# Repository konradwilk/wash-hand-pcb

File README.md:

# License

The project is under Attribution-ShareAlike 4.0 International (CC BY-SA 4.0).

# Libraries used for this project

 - adafruit
 - darnok\_common (https://github.com/konradwilk/eagle-libraries.git)
 - darnok\_led (https://github.com/konradwilk/eagle-libraries.git)
 - darnok\_usb (https://github.com/konradwilk/eagle-libraries.git)
 - darnok\_sensors (https://github.com/konradwilk/eagle-libraries.git)
 - darnok\_microsd (https://github.com/konradwilk/eagle-libraries.git)
 - darnok\_4050 (https://github.com/konradwilk/eagle-libraries.git)
 - SparkFun-Aesthetics
 - SparkFun-Capacitors
 - SparkFun-Connectors
 - SparkFun-Hardware
 - SparkFun-IC-Microcontroller
 - SparkFun-IC-Power
 - SparkFun-Jumpers
 - Serial-Basic (https://github.com/sparkfun/Serial_Basic_Breakout-CH340G.git)

# Purpose

Quite simply it is to have a count-down timer for 20 seconds for washing hands.
It is activated by a line sensor (which has infrared light) that plugs in the board.

</img>

Video (speed up) of text printed.

# PCB

The _main_ branch is for development and changes often.
The <a href="Wash_Hand.pdf">Wash Hand</a> Board and Schematic are available.

## Prior versions

There are various branches, see:

 - <a href="https://github.com/konradwilk/wash-hand-pcb/tree/stable-1.3-tqfp">stable-1.3-tqfp</a>
 - <a href="https://github.com/konradwilk/wash-hand-pcb/tree/stable-1.3-dip28">stable-1.3-dip28</a>
 - <a href="https://github.com/konradwilk/wash-hand-pcb/tree/stable-1.2-dip28">stable-1.2-dip28</a>

# Future plans for software

In particular order:

 - Fetch data from a SD-card (if attached), otherwise read from EEPROM (1K).
 - Format-type of the data type for above mechanism.
 - Utilize sleep operations to keep the CPU most of the time asleep.
 - Utilize modulo for the numbers.

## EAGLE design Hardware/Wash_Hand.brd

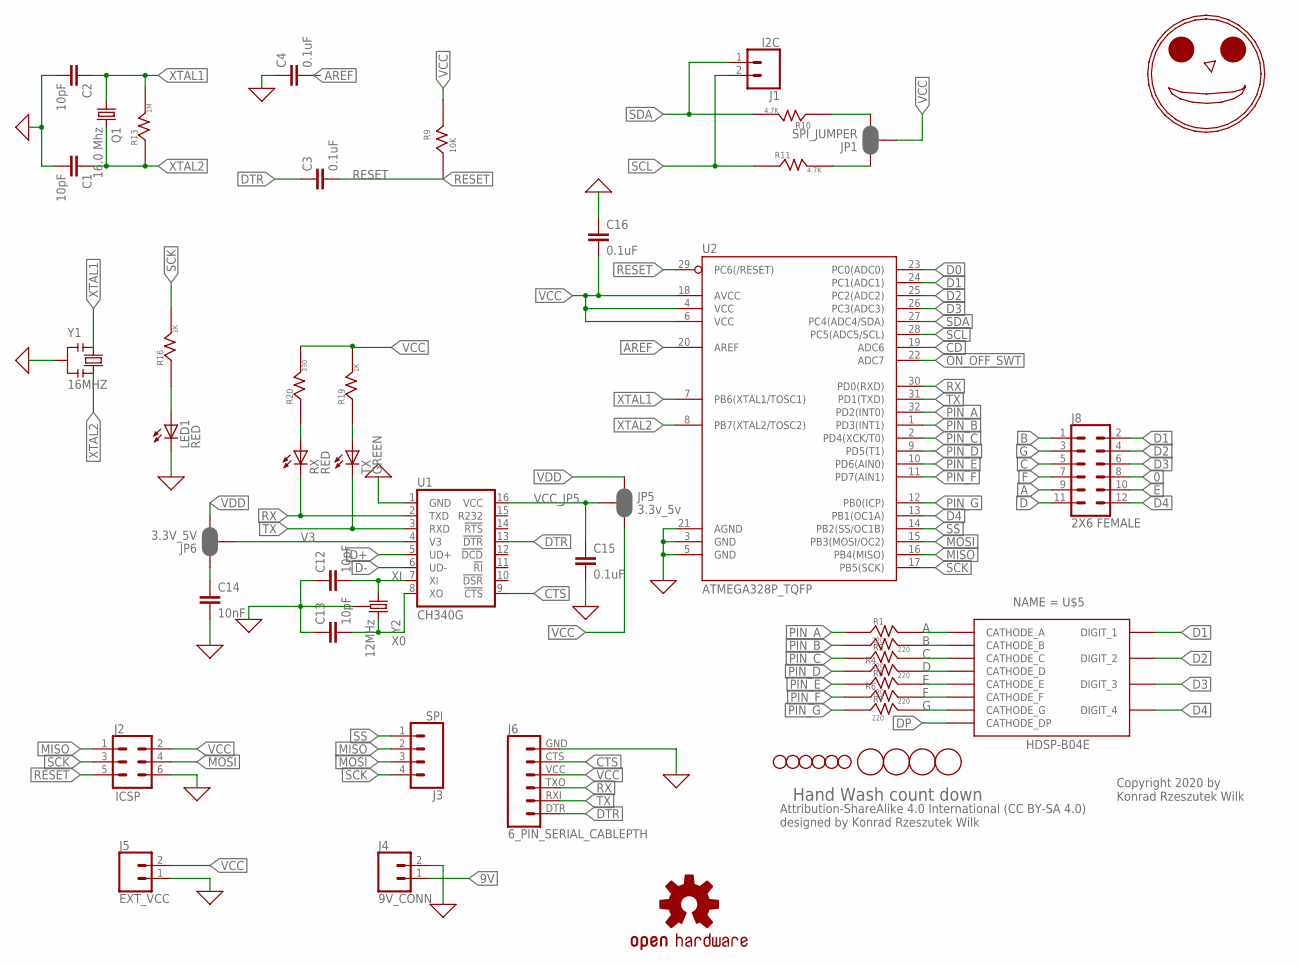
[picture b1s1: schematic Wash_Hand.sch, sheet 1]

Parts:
C1, C2, C12, C13: 10pF; 1206
C3, C4, C15, C16: 0.1uF; 1206
C14: 10nF; 1206
H1, H2, H3, H4, H5, H6: STAND-OFF
J1: I2C; 1X02
J2: ICSP; 2X3
J3: SPI; 1X04
J4: 9V_CONN; 1X02
J5: EXT_VCC; 1X02
J6: 6_PIN_SERIAL_CABLEPTH; FTDI_BASIC
J8: 2X6 FEMALE; 2X6
JP1: SPI_JUMPER; SMT-JUMPER_3_2-NC_PASTE_SILK
JP5: 3.3v_5v; SMT-JUMPER_3_2-NC_PASTE_SILK
JP6: 3.3V_5V; SMT-JUMPER_3_2-NC_PASTE_SILK
LED1: RED; 1206
LOGO1: OSHW-LOGOM; OSHW-LOGO-M
LOGO2: HAPPY_FACE_LOGO
Q1: 16.0 Mhz; HC49/S
R1, R2, R3, R4, R5, R6, R7: 220; 1206
R9: 10K; 1206
R10, R11: 4.7K; 1206
R13: 1M; 1206
R16, R19: 1K; 1206
R20: 330; 1206
RX: RED; 1206
TX: GREEN; 1206
U1: CH340G; SO016
U2: ATMEGA328P_TQFP; TQFP32-08
U$5: HDSP-B04E; HDSP-B0XE
U$7, U$8, U$9, U$10: FIDUCIAL; FIDUCIAL_1MM
Y1: 16MHZ; RESONATOR
Y2: 12MHz; CRYSTAL-SMD-3.2X2.5

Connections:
0: C1.2, C2.2, C4.1, C12.1, C13.1, C14.2, C15.2, C16.1, J2.6, J4.2, J5.1, J6.GND (6), J8.8, LED1.C, U1.1 (GND), U2.3 (GND), U2.5 (GND), U2.21 (AGND), Y1.2, Y2.2 (GND), Y2.4 (GND); also elsewhere on the board
9V: J4.1; also elsewhere on the board
A: J8.9, R1.2 (R_2), U$5.PIN$11 (CATHODE_A)
AREF: C4.2, U2.20 (AREF)
B: J8.1, R2.2 (R_2), U$5.PIN$7 (CATHODE_B)
C: J8.5, R3.2 (R_2), U$5.PIN$4 (CATHODE_C)
CD: U2.19 (ADC6); also elsewhere on the board
CTS: J6.CTS (5), U1.9 (!CTS)
D: J8.11, R4.2 (R_2), U$5.PIN$2 (CATHODE_D)
D0: U2.23 (PC0(ADC0)); also elsewhere on the board
D1: J8.2, U2.24 (PC1(ADC1)), U$5.PIN12 (DIGIT_1)
D2: J8.4, U2.25 (PC2(ADC2)), U$5.PIN$9 (DIGIT_2)
D3: J8.6, U2.26 (PC3(ADC3)), U$5.PIN$8 (DIGIT_3)
D4: J8.12, U2.13 (PB1(OC1A)), U$5.PIN$6 (DIGIT_4)
D+: U1.5 (UD+); also elsewhere on the board
D-: U1.6 (UD-); also elsewhere on the board
DP: U$5.PIN$3 (CATHODE_DP)
DTR: C3.1, J6.DTR (1), U1.13 (!DTR)
E: J8.10, R5.2 (R_2), U$5.PIN$1 (CATHODE_E)
F: J8.7, R6.2 (R_2), U$5.PIN$10 (CATHODE_F)
G: J8.3, R7.2 (R_2), U$5.PIN$5 (CATHODE_G)
MISO: J2.1, J3.2, U2.16 (PB4(MISO)); also elsewhere on the board
MOSI: J2.4, J3.3, U2.15 (PB3(MOSI/OC2)); also elsewhere on the board
unnamed: JP1.3, R10.1 (R_1)
unnamed: JP1.1, R11.2 (R_2)
unnamed: LED1.A, R16.1 (R_1)
unnamed: R19.1 (R_1), TX.A
unnamed: R20.1 (R_1), RX.A
unnamed: C14.1, JP6.1
ON_OFF_SWT: U2.22 (ADC7); also elsewhere on the board
PIN_A: R1.1 (R_1), U2.32 (PD2(INT0))
PIN_B: R2.1 (R_1), U2.1 (PD3(INT1))
PIN_C: R3.1 (R_1), U2.2 (PD4(XCK/T0))
PIN_D: R4.1 (R_1), U2.9 (PD5(T1))
PIN_E: R5.1 (R_1), U2.10 (PD6(AIN0))
PIN_F: R6.1 (R_1), U2.11 (PD7(AIN1))
PIN_G: R7.1 (R_1), U2.12 (PB0(ICP))
RESET: C3.2, J2.5, R9.1 (R_1), U2.29 (PC6(/RESET))
RX: J6.TXO (3), RX.C, U1.2 (TXD), U2.30 (PD0(RXD))
SCK: J2.3, J3.4, R16.2 (R_2), U2.17 (PB5(SCK)); also elsewhere on the board
SCL: J1.2, R11.1 (R_1), U2.28 (PC5(ADC5/SCL))
SDA: J1.1, R10.2 (R_2), U2.27 (PC4(ADC4/SDA))
SS: J3.1, U2.14 (PB2(SS/OC1B)); also elsewhere on the board
TX: J6.RXI (2), TX.C, U1.3 (RXD), U2.31 (PD1(TXD))
V3: JP6.2, U1.4 (V3)
VCC: C16.2, J2.2, J5.2, J6.VCC (4), JP1.2, JP5.3, R9.2 (R_2), R19.2 (R_2), R20.2 (R_2), U2.4 (VCC), U2.6 (VCC), U2.18 (AVCC); also elsewhere on the board
VCC_JP5: C15.1, JP5.2, U1.16 (VCC)
VDD: JP5.1, JP6.3; also elsewhere on the board
X0: C13.2, U1.8 (XO), Y2.3 (2)
XI: C12.2, U1.7 (XI), Y2.1
XTAL1: C2.1, Q1.1, R13.2 (R_2), U2.7 (PB6(XTAL1/TOSC1)), Y1.1
XTAL2: C1.1, Q1.2, R13.1 (R_1), U2.8 (PB7(XTAL2/TOSC2)), Y1.3

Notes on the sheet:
Hand Wash count down
Copyright 2020 by Konrad Rzeszutek Wilk
Attribution-ShareAlike 4.0 International (CC BY-SA 4.0) designed by Konrad Rzeszutek Wilk

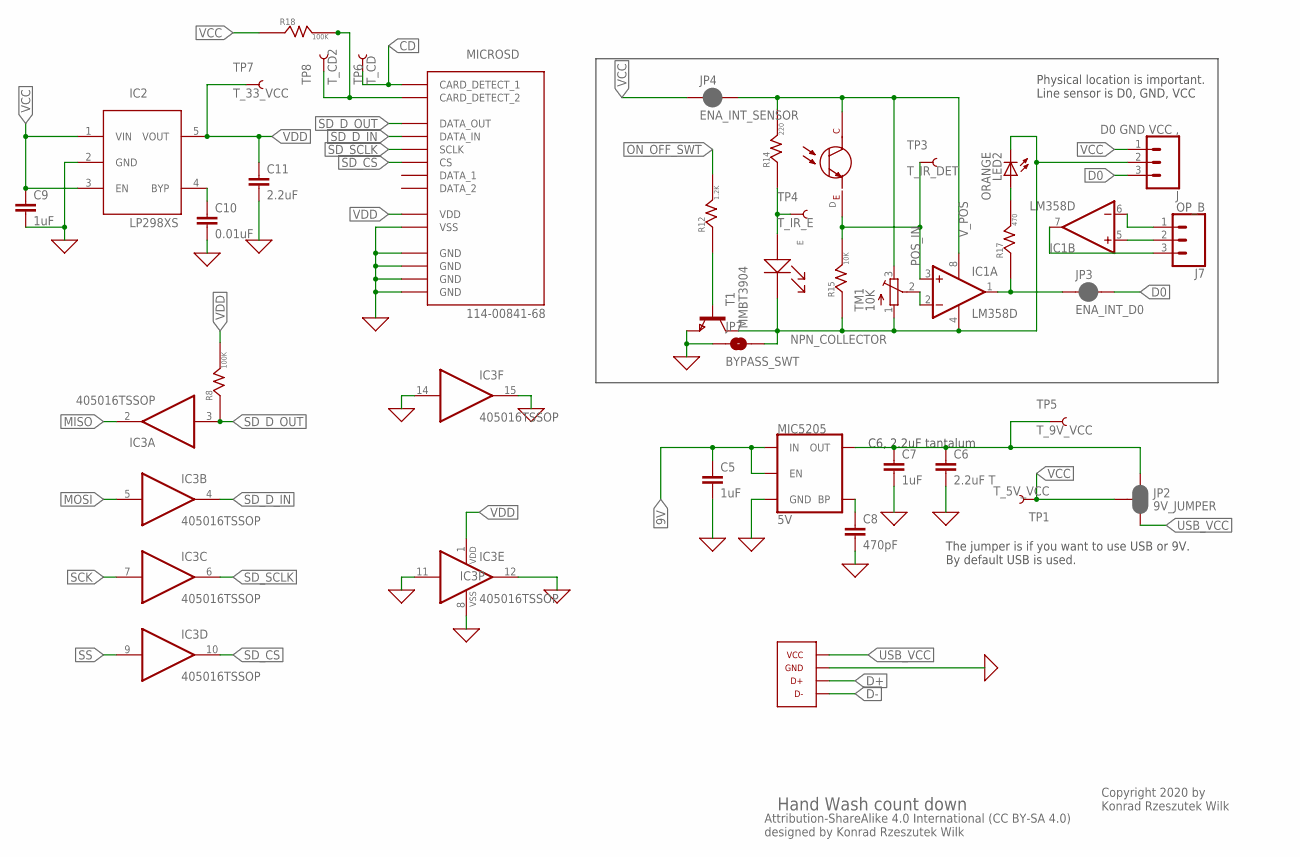
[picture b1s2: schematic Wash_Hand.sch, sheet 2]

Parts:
C5, C7, C9: 1uF; 1206
C6: 2.2uF T; 1206
C8: 470pF; 1206
C10: 0.01uF; 1206
C11: 2.2uF; 1206
D: LTR-301
E: LTE-302
IC1: LM358D; SO08
IC2: LP298XS; SOT23-5L
IC3: 405016TSSOP; TSSOP16
J: D0 GND VCC ,; 1X03
J7: OP_B; 1X03
JP2: 9V_JUMPER; SMT-JUMPER_3_2-NC_PASTE_SILK
JP3: ENA_INT_D0; SMT-JUMPER_2_NC_PASTE_SILK
JP4: ENA_INT_SENSOR; SMT-JUMPER_2_NC_PASTE_SILK
JP7: BYPASS_SWT; SMT-JUMPER_2_NO_SILK
LED2: ORANGE; 1206
MIC5205: 5V; SOT23-5
MICROSD: 114-00841-68
R8, R18: 100K; 1206
R12: 1.2K; 1206
R14: 220; 1206
R15: 10K; 1206
R17: 470; 1206
T1: MMBT3904; SOT-23
TM1: 10K; TC33X
TP1: T_5V_VCC; PAD.03X.04
TP3: T_IR_DET; PAD.03X.04
TP4: T_IR_E; PAD.03X.04
TP5: T_9V_VCC; PAD.03X.04
TP6: T_CD; PAD.03X.04
TP7: T_33_VCC; PAD.03X.04
TP8: T_CD2; PAD.03X.04
U$4: USB_MICROB_10118194_AMPHENOL

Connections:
0: C5.2, C6.2, C7.2, C8.2, C9.2, C10.2, C11.2, IC2.2 (GND), IC3.8 (VSS), IC3.11 (I), IC3.12 (O), IC3.14 (I), IC3.15 (O), JP7.1, MIC5205.2 (GND), MICROSD.GND$1 (GND), MICROSD.GND$2 (GND), MICROSD.GND$3 (GND), MICROSD.GND$4 (GND), MICROSD.VSS, T1.2 (E), U$4.5 (GND); also elsewhere on the board
9V: C5.1, MIC5205.1 (IN), MIC5205.3 (EN); also elsewhere on the board
CD: MICROSD.CD_SW_1 (CARD_DETECT_1), TP6.P$1; also elsewhere on the board
D0: IC1.1 (OUT), J.3, JP3.1, JP3.2, R17.1 (R_1); also elsewhere on the board
D+: U$4.3 (D+); also elsewhere on the board
D-: U$4.2 (D-); also elsewhere on the board
MISO: IC3.2 (O); also elsewhere on the board
MOSI: IC3.5 (I); also elsewhere on the board
unnamed: IC1.7 (OUT), J7.3
unnamed: MICROSD.CD_SW_2 (CARD_DETECT_2), R18.2 (R_2), TP8.P$1
unnamed: IC1.5 (+IN), J7.2
unnamed: C6.1, C7.1, JP2.1, MIC5205.5 (OUT), TP5.P$1
unnamed: E.A, R14.1 (R_1), TP4.P$1
unnamed: C10.1, IC2.4 (BYP)
unnamed: IC1.6 (-IN), J7.1
unnamed: LED2.A, R17.2 (R_2)
unnamed: R12.1 (R_1), T1.3 (B)
unnamed: C8.1, MIC5205.4 (BP)
NEG_IN: IC1.2 (-IN), TM1.2 (S)
NPN_COLLECTOR: E.C, IC1.4 (V-), J.2, JP7.2, LED2.C, R15.1 (R_1), T1.1 (C), TM1.1 (A)
ON_OFF_SWT: R12.2 (R_2); also elsewhere on the board
POS_IN: D.E, IC1.3 (+IN), R15.2 (R_2), TP3.P$1
SCK: IC3.7 (I); also elsewhere on the board
SD_CS: IC3.10 (O), MICROSD.CS
SD_D_IN: IC3.4 (O), MICROSD.DATA_IN
SD_D_OUT: IC3.3 (I), MICROSD.DATA_OUT, R8.1 (R_1)
SD_SCLK: IC3.6 (O), MICROSD.SCLK
SS: IC3.9 (I); also elsewhere on the board
USB_VCC: JP2.3, U$4.1 (VCC)
VCC: C9.1, IC2.1 (VIN), IC2.3 (EN), J.1, JP2.2, JP4.1, R18.1 (R_1), TP1.P$1; also elsewhere on the board
VDD: C11.1, IC2.5 (VOUT), IC3.1 (VDD), MICROSD.VDD, R8.2 (R_2), TP7.P$1; also elsewhere on the board
V_POS: D.C, IC1.8 (V+), JP4.2, R14.2 (R_2), TM1.3 (E)

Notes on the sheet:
Hand Wash count down
Copyright 2020 by Konrad Rzeszutek Wilk
Attribution-ShareAlike 4.0 International (CC BY-SA 4.0) designed by Konrad Rzeszutek Wilk
Physical location is important. Line sensor is D0, GND, VCC
The jumper is if you want to use USB or 9V. By default USB is used.
C6, 2.2uF tantalum

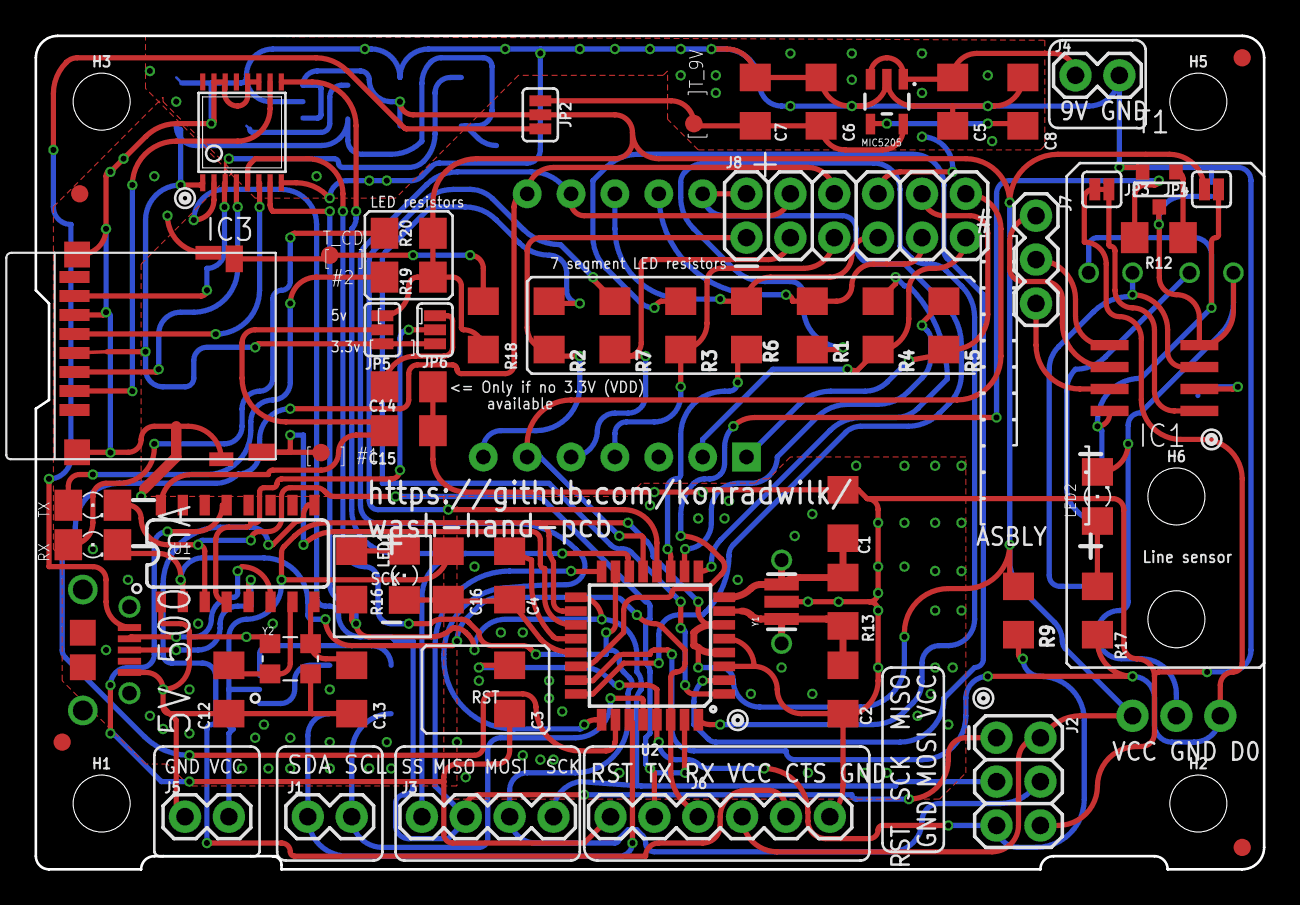
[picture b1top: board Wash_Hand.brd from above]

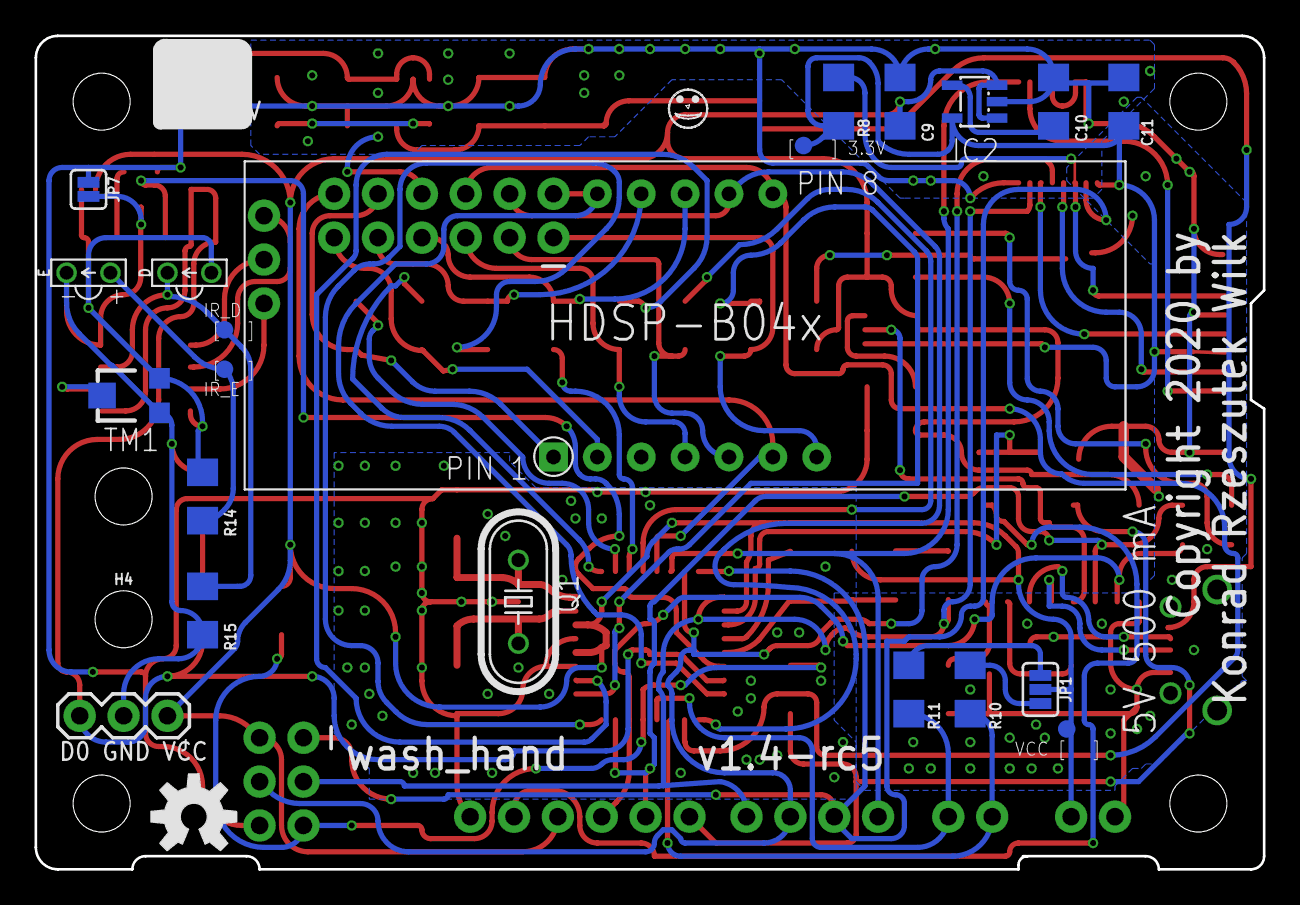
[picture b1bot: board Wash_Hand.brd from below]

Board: 2 copper layers, 71.1 x 48.3 mm, 91 parts (24 on the bottom side), 70 nets.

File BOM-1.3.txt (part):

Partlist exported from /home/konrad/eagle-projects/COVID19-WashHands/Hardware/Wash_Hand_v1.3.sch at 8/14/20 10:20 PM

Qty Value                        Device                        Package                       Parts                           Description                                                                                                                                                                                                                                             HDSP-B04E MF MPN OC_FARNELL OC_NEWARK POPULARITY PROD_ID    VALUE     
1                                CONN_02                       1X02                          J4                              Multi connection point. Often used as Generic Header-pin footprint for 0.1 inch spaced/style header connections                                                                                                                                                                                                               
1   0.01uF                       1.0UF-1206-50V-10%            1206                          C10                             1µF ceramic capacitors                                                                                                                                                                                                                                                                                   CAP-09822  1.0uF     
2   0.1uF                        1.0UF-1206-50V-10%            1206                          C3, C4                          1µF ceramic capacitors                                                                                                                                                                                                                                                                                   CAP-09822  1.0uF     
1   100K                         RESISTORR1206                 1206                          R8                                                                                                                                                                                                                                                                                                                                                            
2   10K                          RESISTORR1206                 1206                          R9, U$1                                                                                                                                                                                                                                                                                                                                                       
1   10K                          TRIMPOTTC33X                  TC33X                         TM1                             SMT trimmer potentiometer part number TC33X                                                                                                                                                                                                                                                                                   
1   114-00841-68                 114-00841-68                  114-00841-68                  MICROSD                         Amphenol MicroSD Push Pull                                                                                                                                                                                                                                                                                                    
1   16.0 Mhz                     CRYSTALHC49S                  HC49/S                        Q1                              CRYSTAL                                                                                                                                                                                                                                                                  1667008    unknown                                   
3   1uF                          1.0UF-1206-50V-10%            1206                          C5, C7, C9                      1µF ceramic capacitors                                                                                                                                                                                                                                                                                   CAP-09822  1.0uF     
2   2.2uF                        1.0UF-1206-50V-10%            1206                          C6, C8                          1µF ceramic capacitors                                                                                                                                                                                                                                                                                   CAP-09822  1.0uF     
8   220                          RESISTORR1206                 1206                          R1, R2, R3, R4, R5, R6, R7, U$2                                                                                                                                                                                                                                                                                                                               
2   22pF                         10UF-1206-6.3V-20%            1206                          C1, C2                          10.0µF ceramic capacitors                                                                                                                                                                                                                                                                                CAP-10057  10uF      
1   328P                         ATMEGA328P_PDIP               DIP28                         U1                              Atmel 328P                                                                                                                                                                                                                                                                                               IC-09136   328P      
2   4.7K                         RESISTORR1206                 1206                          R10, R11                                                                                                                                                                                                                                                                                                                                                      
1   4050D                        4050D                         SO16                          IC3                             Hex non-inverting BUFFER                                                                                                                                                                                                                                                                      6                               
1   470pF                        1.0UF-1206-50V-10%            1206                          C11                             1µF ceramic capacitors                                                                                                                                                                                                                                                                                   CAP-09822  1.0uF     
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
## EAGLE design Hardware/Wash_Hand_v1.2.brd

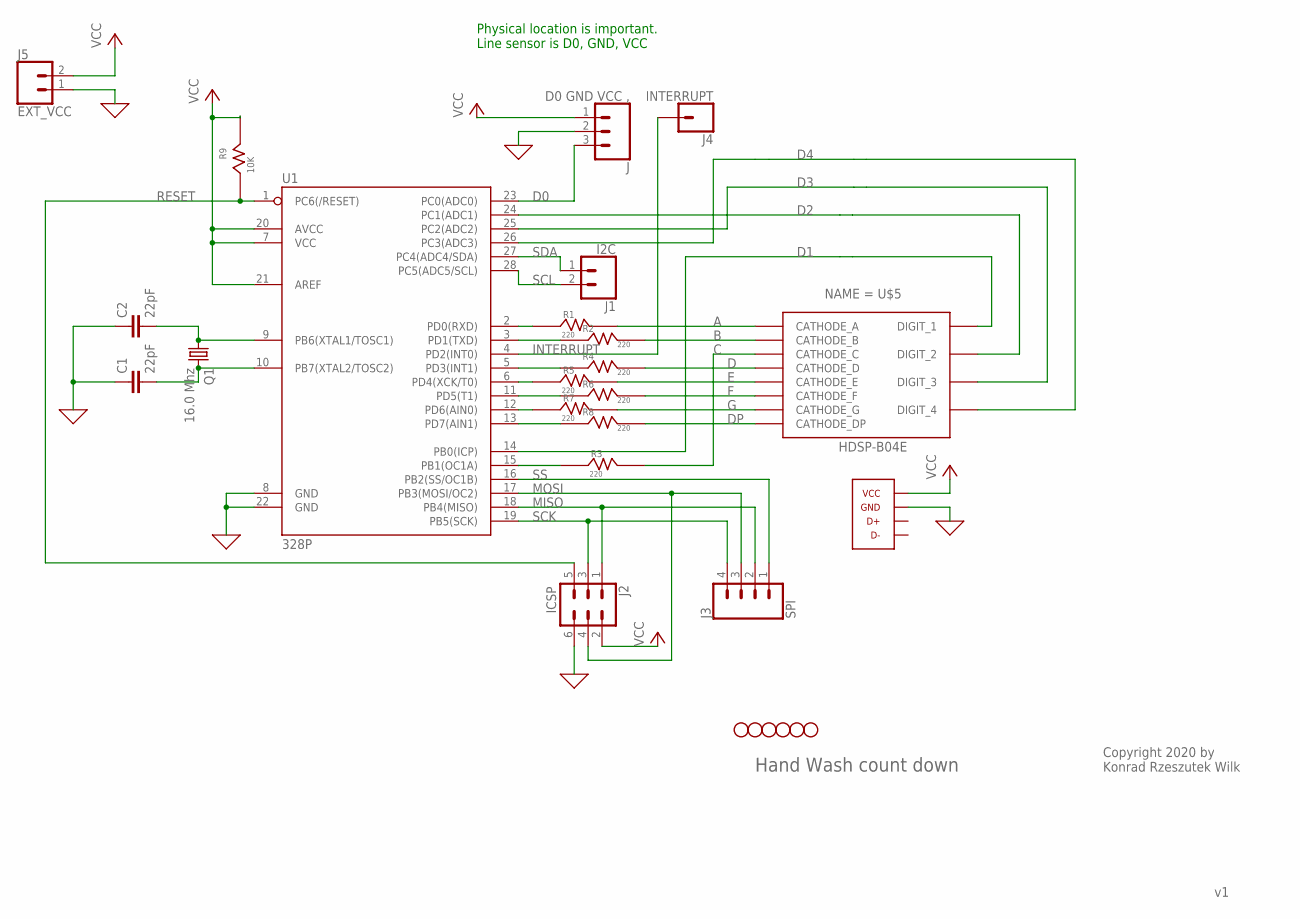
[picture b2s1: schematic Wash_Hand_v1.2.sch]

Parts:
C1, C2: 22pF; CAP-PTH-2.54
H1, H2, H3, H4, H5, H6: STAND-OFF
J: D0 GND VCC ,; 1X03
J1: I2C; 1X02
J2: ICSP; 2X3
J3: SPI; 1X04
J4: INTERRUPT; 1X01
J5: EXT_VCC; 1X02
Q1: 16.0 Mhz; HC49/S
R1, R2, R3, R4, R5, R6, R7, R8: 220; RESISTOR
R9: 10K; RESISTOR
U1: 328P; DIP28
U$4: USB_MICROB_10118194_AMPHENOL
U$5: HDSP-B04E; HDSP-B0XE

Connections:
0: C1.1, C2.1, J.2, J2.6, J5.1, U1.8 (GND), U1.22 (GND), U$4.5 (GND)
A: R1.R_2, U$5.PIN$11 (CATHODE_A)
B: R2.R_2, U$5.PIN$7 (CATHODE_B)
C: R3.R_2, U$5.PIN$4 (CATHODE_C)
D: R4.R_2, U$5.PIN$2 (CATHODE_D)
D0: J.3, U1.23 (PC0(ADC0))
D1: U1.14 (PB0(ICP)), U$5.PIN12 (DIGIT_1)
D2: U1.24 (PC1(ADC1)), U$5.PIN$9 (DIGIT_2)
D3: U1.25 (PC2(ADC2)), U$5.PIN$8 (DIGIT_3)
D4: U1.26 (PC3(ADC3)), U$5.PIN$6 (DIGIT_4)
DP: R8.R_2, U$5.PIN$3 (CATHODE_DP)
E: R5.R_2, U$5.PIN$1 (CATHODE_E)
F: R6.R_2, U$5.PIN$10 (CATHODE_F)
G: R7.R_2, U$5.PIN$5 (CATHODE_G)
INTERRUPT: J4.1, U1.4 (PD2(INT0))
MISO: J2.1, J3.2, U1.18 (PB4(MISO))
MOSI: J2.4, J3.3, U1.17 (PB3(MOSI/OC2))
unnamed: R3.R_1, U1.15 (PB1(OC1A))
unnamed: R1.R_1, U1.2 (PD0(RXD))
unnamed: R5.R_1, U1.6 (PD4(XCK/T0))
unnamed: R7.R_1, U1.12 (PD6(AIN0))
unnamed: C1.2, Q1.2, U1.10 (PB7(XTAL2/TOSC2))
unnamed: C2.2, Q1.1, U1.9 (PB6(XTAL1/TOSC1))
unnamed: R8.R_1, U1.13 (PD7(AIN1))
unnamed: R6.R_1, U1.11 (PD5(T1))
unnamed: R4.R_1, U1.5 (PD3(INT1))
unnamed: R2.R_1, U1.3 (PD1(TXD))
RESET: J2.5, R9.R_1, U1.1 (PC6(/RESET))
SCK: J2.3, J3.4, U1.19 (PB5(SCK))
SCL: J1.2, U1.28 (PC5(ADC5/SCL))
SDA: J1.1, U1.27 (PC4(ADC4/SDA))
SS: J3.1, U1.16 (PB2(SS/OC1B))
VCC: J.1, J2.2, J5.2, R9.R_2, U1.7 (VCC), U1.20 (AVCC), U1.21 (AREF), U$4.1 (VCC)

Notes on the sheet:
Physical location is important. Line sensor is D0, GND, VCC
Hand Wash count down
Copyright 2020 by Konrad Rzeszutek Wilk

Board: 2 copper layers, 27 parts (3 on the bottom side), 33 nets, no tracks yet.

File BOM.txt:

Partlist exported from /home/opc/EAGLE/projects/COVID19-WashHands/Hardware/Wash_Hand_v1.2-routing.sch at 7/14/20 2:54 AM

Qty Value                        Device                       Package                      Parts                          Description                                                                                                      HDSP-B04E MF MPN OC_FARNELL OC_NEWARK PROD_ID    VALUE     
1   10K                          RESISTOR                     RESISTOR                     R9                                                                                                                                                                                                         
1   16.0 Mhz                     CRYSTALHC49S                 HC49/S                       Q1                             CRYSTAL                                                                                                                           1667008    unknown                        
8   220                          RESISTOR                     RESISTOR                     R1, R2, R3, R4, R5, R6, R7, R8                                                                                                                                                                             
2   22pF                         22PF-PTH-2.54MM-200V-5%      CAP-PTH-2.54                 C1, C2                         22pF ceramic capacitors                                                                                                                                CAP-09128  22pF      
1   328P                         ATMEGA328P_PDIP              DIP28                        U1                             Atmel 328P                                                                                                                                             IC-09136   328P      
1   D0    GND  VCC  ,            CONN_03                      1X03                         J                              Multi connection point. Often used as Generic Header-pin footprint for 0.1 inch spaced/style header connections                                                             
1   EXT_VCC                      CONN_02                      1X02                         J5                             Multi connection point. Often used as Generic Header-pin footprint for 0.1 inch spaced/style header connections                                                             
1   HDSP-B04E                    HDSP-B04E                    HDSP-B0XE                    U$5                            7 Segment LED light 0.56"                                                                                                                                                   
1   I2C                          CONN_02                      1X02                         J1                             Multi connection point. Often used as Generic Header-pin footprint for 0.1 inch spaced/style header connections                                                             
1   ICSP                         CONN_03X2FEMALE              2X3                          J2                             Multi connection point. Often used as Generic Header-pin footprint for 0.1 inch spaced/style header connections                                        CONN-11566 FEMALE 2x3
1   INTERRUPT                    CONN_01                      1X01                         J4                             Single connection point. Often used as Generic Header-pin footprint for 0.1 inch spaced/style header connections                                                            
1   SPI                          CONN_04                      1X04                         J3                             Multi connection point. Often used as Generic Header-pin footprint for 0.1 inch spaced/style header connections                                        CONN-09696           
6   STAND-OFF                    STAND-OFF                    STAND-OFF                    H1, H2, H3, H4, H5, H6         Stand Off                                                                                                                                                                   
1   USB_MICROB_10118194_AMPHENOL USB_MICROB_10118194_AMPHENOL USB_MICROB_10118194_AMPHENOL U$4

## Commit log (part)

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2020-07-14 LICENSE: Attribution-ShareAlike 4.0 International (CC BY-SA 4.0).
2020-07-14 Initial schematic and board design.
    v1.1 is bad. I made the auto-routing , added some new items and it has
    now no linking to the schematic. Ignore it.
    v1.2 is the right one.
2020-07-14 Software: Add SPDX
2020-07-14 Initial README file outlaying the ambitions of this project.
2020-07-14 README: Include BOM and URL to line sensor
2020-07-23 Hardware: Split out using darnok_[common,led,usb] instead of the single one.
    As the darnok_misc is going away.
2020-07-23 Hardware: Switch to TQFP32 on ATMEGA328P
2020-07-23 Hardware: Add resistors (4.7K) for the I2C along with a pad.
    The pad is there in case we don't want to use the pull-up
    resistors.
2020-07-23 Hardware: Add OSHW Logo.
2020-07-23 Schematic: Move the information tag to tDoc layer.
2020-07-23 README: Update the list of libraries we use.
2020-07-28 v1.2: Assembly notes.
    Biggest issues:
    - Missing PIN1 label on the ICSP header.
    - The ICSP header should be turned 90
    - Holes for the LED are mighty small
    - No 0.1 uF between pin 7,8 and 20,22
    - Putting in a ATMEGA328P from a Uno works, but programming via SPI no go.
2020-07-29 Makefile: Add makefile using arduino-cli
    Installation:
    https://arduino.github.io/arduino-cli/installation/
2020-07-29 software: Remove the spaces
2020-07-29 Software: Move all the GPIO code in seperate header.
2020-07-30 Software: Add USB only interface
    To easy in debugging.
2020-07-30 Software: s/NOBODY/INIT/
    Better name.
2020-07-30 Software: Add debug_error to signal issues
    We should not hit those code paths - but if we do
    print out the line number.
2020-07-30 Software: Add delay for the second digit (1x, 20)
    Otherwise it would be less brigther than the other one.
2020-07-30 Software: debug: Add __LINE__
    to make it easier to troubleshoot where it is in the code.
2020-07-30 TODO: The code could be improved.
2020-07-30 Notes: For programming with USB we will need RX, TX pins
    But those are used for PINA, and PINB so we will need
    to relocate those two. We don't use DP.
2020-08-01 Schematic: Move the HDSP-B04E to v1.2 location.
    As we also want to re-use the same case for both versions.
2020-08-01 v1.3: Remove INT and DP connection, and attach A, B pins to
2020-08-02 Board/Schematic: Add SCK label and connect to pins
2020-08-03 Board Schematic: Add SS and connect the headers to this label
2020-08-03 Schematic: Move the SPI header to its own location
2020-08-03 Schematic: Add junction on the ground plane.
2020-08-03 Schematic: Move HDSP-B04E and do some cleanups.
2020-08-03 Schematic: Add decoupling capacitor on the VREF.
2020-08-03 Board: Add FTDI basic (6 pin).
    And connect them all.
2020-08-03 Board: Move text around as pin placement will poke through it.
2020-08-04 Board/Schematic: Add line sensor.
    We are using QRE1113GR.
2020-08-07 Board: Change to different line sensor.
    We are going to use discrete parts:
    - LTE-302, LTR-301 (IR emitter and detector).
    - TC33X-2-103E 10K pot
    - LM358DR
    - Bunch of SMD resistors
    This should us give better range.
2020-08-08 Schematic: Add extra sheet.
    We can't just fit any more on just one.
2020-08-08 Board: Adjust the D0_JUMPER,VCC_JUMPER, SPI_JUMPER to the right.
2020-08-09 Board/Schematic: s/VCC/VCC label/
    As that makes it easier to switch in/out componets.
2020-08-10 Board: Move parts around so capacitors are close to LP298 and MIC52055
    Both specs say that capacitors have to be within 0.5 inch.
2020-08-10 Board: All test points have text around them.
2020-08-10 Board: Move Copyright and update date.
2020-08-10 Board/Schematic: Add 470pF bypass to MIC5205
    And also change the Cout to be 2.2uF
2020-08-11 Board: Remove little space for fingers to eject MicroSD card.
2020-08-12 Board/Schematic: Add ATMEGA328P TQFP with goal of replacing DIP28
    .. so that we can swap in and out the DIP28 or TQFP for the prototype
    builds.
2020-08-15 Board: Routing #1
    - We moved a lot of resistors and capacitors around to be
    closer.
    - Realized we can do two "v1.3" - one with a DIP28 and
    one with TQFP. Most of the routes would hopefully lead to the
    right locations.
2020-08-15 Schematic: Fix C5 not being connected (found during routing).
    Somehow the lines did not connect so it just ended up being
    not connected. This fixes it.
2020-08-15 Revert: "Board/Schematic: Add ATMEGA328P TQFP with goal of replacing DIP28"
    .. with the rest of the items to not confuse readers.
2020-08-15 Board: Use the TQFP instead of DIP-28. Change version to have -b postfix.
2020-08-16 Documentation: Update on v1.3a board.
2020-08-26 README: Fix up version number (it is 1.3b)
2020-09-02 Board: Make the SMD register names smaller.
    They are huge.
2020-09-02 Board/Schematic: Update to v1.3b.1
2020-09-02 Board/Schematic: Swap out 4050 to 16TSSOP
    instead of the more bulkier SOP16
2020-09-03 Board: Add + for the tantalum capacitor
2020-09-03 Board: Add PIN1 easy dot for LM358 and ATMEGA328P
2020-09-05 Schematic: PIN1 on LP298 was not hooked to VCC
    .. but it was on the board!
2020-09-05 Schematic: Nothing is connected to ADC6,7 so delete the nets.
2020-09-05 Schematic: Update libraries ...
2020-09-05 Board/Schematic: Update to v1.3b_rc4
2020-09-07 Software: Fix the warnings over __LINE__
2020-09-07 Software: We are using v1.3 ports
2020-09-09 Board/Schematic: Change 22pf to 10pf
    Which makes the crystal work..
2020-09-14 Software: Debug mode - only print 1,2,3,8 once and then
    go in regular mode.
2020-09-15 Board/Schematic: Fix the 16MHz/10pF capacitors.
    The way they are were in the schematic looked right.
    Two capacitors off the crystal. Both capacitors go to
    ground. Except that what Eagle decided it should be was:
    XTAL1 XTAL2
    | |
    +--[CRYSTAL]--+
2020-09-15 Board: Swap C7 with C9.
    The LP298 has C9,C10,C11 but in the board right next to it are:
    _C7_,C10,C11!
    The MIC5205 has C5,C6,C7,C8 but in the board right next to it
    are: C5,C6,_C9_, and C8.
    Lets swap them around to be closer to their own circuits.
2020-09-16 Software: Add USBasp upload
2020-09-16 Release: v1.3a.3
2020-09-16 Board/Schematic: Add resonator (on top of crystal)
    So that we can use either the resonator or
    the crystal+capacitor.
2020-09-22 Board: Add USB ground plane.
    And connect it with the other two.
2020-09-22 Board: Add ground plane for 9V and 3.3V power plants
    They are connected up there..
2020-09-22 Remove the old versions (v1.2, v1.1, and v1).
    If folks want to see them, there will be branches:
    stable-1.2 (DIP28)
    stable-1.3-dip28 (DIP28)
    stable-1.3-tqfp
2020-09-22 Wash_Hand v1.3 -> Wash_Hand
    since we are using Git the release name does not make much sense
    anymore.
2020-09-22 Board: Flip 7Segment resistors
    .. and also some DRC errors.
2020-09-22 Board: Fixup the registers name and values.
    Align the names and values to be next to each other.
2020-09-22 Board/Schematic: Major rework:
    - Move the TQFP so that we can have the crystal right next to it.
    - Move most of the data lines to one side of the board.
    - Move resistors / capacitors around around the components
    - Make the wires 0.012 instead of 0.006 (or 0.008).
    - Also while we are it, make the turns more curved.
    Next:
2020-09-22 Board/Schematic: Update RELEASE to be main
    As that is the current release train.
2020-09-22 Release: By default assume Hardware/Wash_Hand.sch
    in case that is not provided.
2020-09-22 Release: Remove the print option
    And instead run the print.scr
2020-09-22 Software: Add printk(..)
    to make it easier to write strings.
2020-09-22 USBAsp: Corruptions on verify
    .. are sometimes seen. Doing a full erase flash fixes
    the issue.
2020-09-24 Software: DEBUG - make printing faster..
    to easy debugging.
2020-09-25 Board/Schematic: Add a LED on the line-sensor
    ..when we have detected a change.
2020-09-25 RELEASE-1.4-rc0
2020-10-16 Schematic/Board: Move the CH340 to right and use smaller 12Mhz SMD clock
2020-10-17 Board/Hardware: Add 5V support for CH340
    ..which requires adding jumpers and a capacitor (0.01uF).
    While at it, add the power decoupling one for VCC.
2020-10-17 Schematic/Board: Add 100nF decoupling capacitor to AVCC
2020-10-17 RELEASE-1.4-rc1
2020-10-31 Software: Build always with DEBUG, NOSD, and Watchdog.
2020-10-31 Makefile: Roll up the various defines and define variables
2020-11-04 Makefile: Target for ATMEGA8 as well
2020-11-04 Makefile: Add atmega[8,328], and atmega[8,328]_isp targets
    .. which allows us to flash the fuses, load the boatloader
    and then the application in one go.
    Much work copied from optiboot Makefile
2020-11-10 Makefile: Add for ATMEGA8 options for USBASP and USB
2020-11-15 Board/Schematic: Name the nets on the CH340G/Adjust location of GREEN,RED,CH340G
    .. to make it easier to trace and diagnose.
2020-11-15 Schematic: Add circles for pin1 on CH340G and 12Mhz crystal
2020-12-08 Board/Schematic: s/LED3,LED4/TX,RX/
    as it makes it much simpler to figure out on the board.
2020-12-08 Board/Schematic: Line Sensor: Swap 10K with PIR sensor
    I had the 10K with PIR sensor inverted. That is
    the voltage would go down when we are in dark room (so
    nothing to detect), and go above the Vref (aka the
    10K pot on NEG_IN) and light up the LED.
    We need it the other way around - that is in dark
    rooms (so PIR is 20K ohm ,or 7.8K ohm) we want the
2020-12-11 Board/Schematic: Add PNP to turn on/off the line sensor
    .. which we don't have to have on all the time.
2020-12-11 Board/Schematic: Rotate LED2 around..
    We been soldering it the right way but the schematic
    has it turned around.
2020-12-11 Board/Schematic: Add 1.2K resistor to transistor
2020-12-11 Board/Schematic: Add 1.2K resistor to transistor - in correct place
    This fixes the "Board/Schematic: Add 1.2K resistor to transistor" and
    adds the resistor on the correct side of the transitor.
2020-12-11 RELEASE-1.4-rc3
2020-12-27 Board/release/3d: Add housing to the exported images..
    which along with the dimensions can be exported to BMP
    and then converted to STL files for helping to create
    a box for it.
    The sequence is as follow:
    - Install Inkscape 0.92 (don't use 1.01) as the extension does not work
    with later versions.
2020-12-28 3d:Add README.md for the steps.
2020-12-29 Board/Schematic: Remove the v1.4-rc0 from the descriptions.
2020-12-29 Board/Schematic: Add HAPPY_FACE logo
    .. because 2021 is right around the corner!
2021-01-02 Board: Cut in the board to make space for the tabs in
    .. the enclosure.
    (See
    https://github.com/konradwilk/wash-hand-3d-box/blob/main/Wash_Hand.stl)
2021-04-17 Board/Design: Replace PNP with NPN
    And also re-route the ground since the NPN will now
    control whether this whole thing is going to be on/off.
2021-04-17 Board/Schematic: Route Orange LED2 to NPN_COLLECTOR
    instead of the common ground. This way when we disable
    the ON_OFF_SWT the light will not be light up.
2021-04-17 Board/Schematic: Add values and move text around a bit
    so that it is not over the board.
2021-04-21 Add tool to create PnP list based on BOM list
2021-04-21 BOM: Swap out ATMEGA328 with ATMEGA8
    since we don't need all that processing power
    on this revision.
2021-04-22 create_pnp: Create for both JLCPCB and PCBway
    since both use different spreadsheet formats.
2021-04-22 CAM: Get PnP from Eagle in CSV, BOM from ours
    .. instead of the Eagle generated one.
2021-04-22 BOM: Swap out CH340G to Jiangsu Qin Heng

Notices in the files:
parts and their libraries:
SparkFun-Capacitors: Licensing: Creative Commons ShareAlike 4.0 International - https://creativecommons.org/licenses/by-sa/4.0
darnok_sensors: Licensed under the Attribution-ShareAlike 4.0 International (CC BY-SA 4.0).
Copyright 2020 by Konrad Rzeszutek Wilk <konrad@darnok.org></p
